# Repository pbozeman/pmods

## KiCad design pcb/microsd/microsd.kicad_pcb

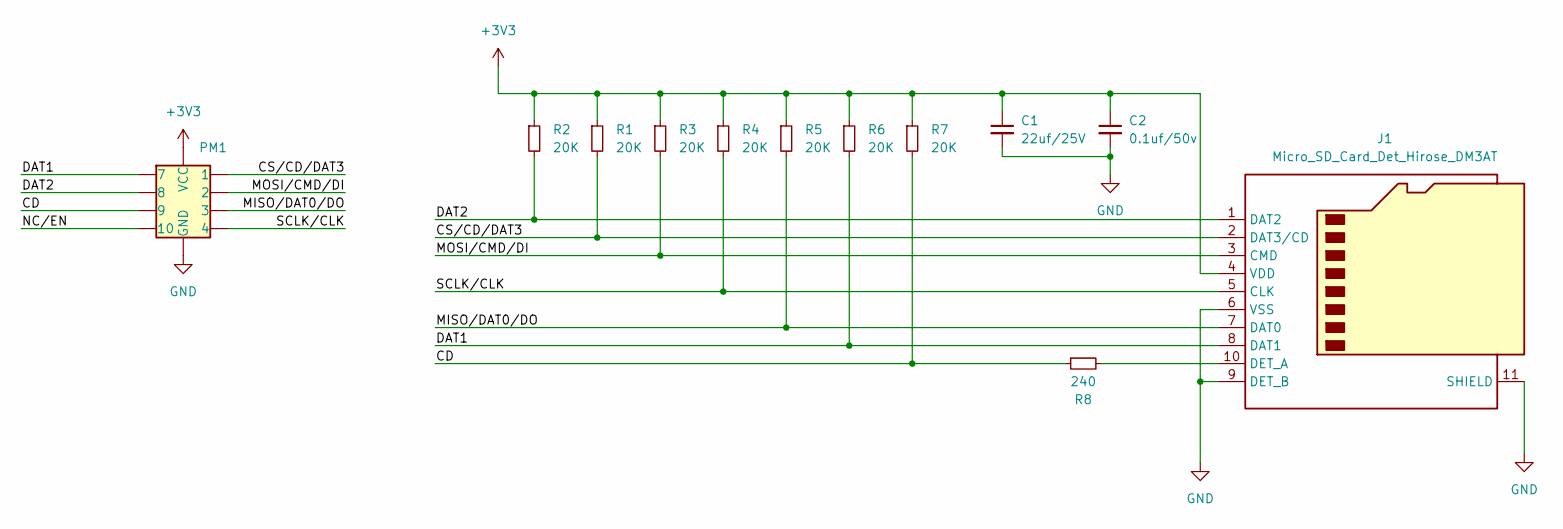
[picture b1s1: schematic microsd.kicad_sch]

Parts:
C1: 22uf/25V; C_0805_2012Metric; LCSC Part # C45783
C2: 0.1uf/50v; C_0603_1608Metric; LCSC Part # C14663
J1: Micro_SD_Card_Det_Hirose_DM3AT; HRS_DM3AT-SF-PEJM5; LCSC Part # C114218
PM1: PMOD_Dual_Male
R1, R2, R3, R4, R5, R6, R7: 20K; R_0603_1608Metric; LCSC Part # C4184
R8: 240; R_0603_1608Metric; LCSC Part # C23350

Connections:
+3V3: C1.1, C2.1, J1.4 (VDD), PM1.6 (VCC), PM1.12 (VCC), R1.1, R2.1, R3.1, R4.1, R5.1, R6.1, R7.1
/CD: PM1.9, R7.2, R8.1
/CS/CD/DAT3: J1.2 (DAT3/CD), PM1.1, R1.2
/DAT1: J1.8 (DAT1), PM1.7, R6.2
/DAT2: J1.1 (DAT2), PM1.8, R2.2
/MISO/DAT0/DO: J1.7 (DAT0), PM1.3, R5.2
/MOSI/CMD/DI: J1.3 (CMD), PM1.2, R3.2
/NC/EN: PM1.10
/SCLK/CLK: J1.5 (CLK), PM1.4, R4.2
GND: C1.2, C2.2, J1.6 (VSS), J1.9 (DET_B), J1.11 (SHIELD), PM1.5 (GND), PM1.11 (GND)
unnamed: J1.10 (DET_A), R8.2

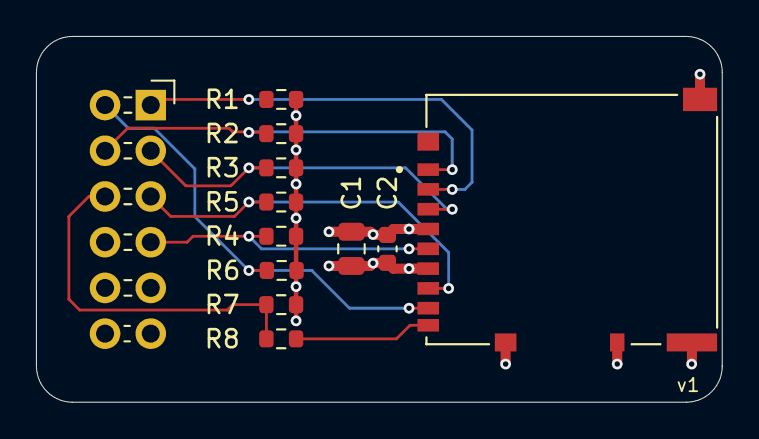
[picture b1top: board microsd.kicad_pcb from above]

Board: 4 copper layers, 38.1 x 20.3 mm, 12 parts (0 on the bottom side), 10 nets.

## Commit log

2026-03-05 [readme] initial commit
2026-03-05 [base] add kicad-base
2026-03-05 [microsd] template
2026-03-05 [microsd] add v1 microsd
